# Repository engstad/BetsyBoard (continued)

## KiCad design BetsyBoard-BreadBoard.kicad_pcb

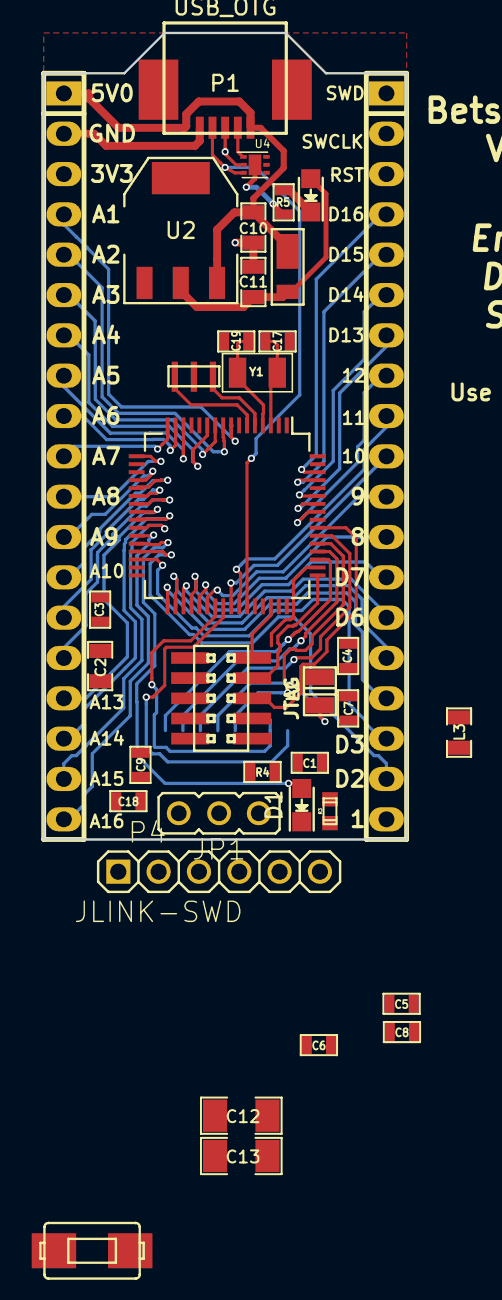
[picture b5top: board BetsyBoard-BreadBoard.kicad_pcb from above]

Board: 2 copper layers, 22.9 x 50.8 mm, 37 parts (1 on the bottom side), 60 nets.

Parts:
C1, C5, C6, C7, C8, C9, C18: 0.1uF; SM0603
C2: 4.7uF; SM0805
C3, C4: 1.0uF; SM0603
C10, C11: 10uF; SM0805
C12, C13: 22uF; SM1206
C17, C19: 10pF; SM0603
CON1: SDMMC_Card; SCHD3A0100
D1: RED; LED-0805
D2: DFLS240L; diode-smd-powerdi-123
D3: GREEN; LED-0805
JP1: JUMPER3; xess-JP2
L2: 470nF; inductor_smd_0805
L3: Bead; SM0805
P1: USB_OTG; usb-otg-short
P2, P3: CONN_01X19; pin_strip_19
P4: JLINK-SWD; HDR_1x6
P6: JTAG; conn-jtag-0.05
R3: 470; r_0603
R4: 10k; SM0603
R5: 470; SM0603
SW1: SW_PUSH; tactile-switch-te-147873-2
U1: STM32L486Rx-LQFP64; LQFP-64_10x10mm_Pitch0.5mm
U2: NCP1117ST33T3G; SOT-223
U4: PUSBM5V5X4; dfn1616-6
X1: XTAL; cstce-v-c
Y1: Crystal; CRYSTAL-32k-B

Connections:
+3.3VADC: C4.1, C9.1, L3.2, U1.13
/A1: P3.4, U1.8
/A2: P3.5, U1.9
/A3: P3.6, U1.10
/A4: P3.7, U1.11
/A5: P3.8, U1.14
/A6: P3.9, U1.15
/A7: P3.10, U1.16
/A8: P3.11, U1.17
/A9: P3.12, U1.20
/A10: P3.13, U1.21
/A11: P3.14, U1.22
/A12: P3.15, U1.23
/A13: P3.16, U1.24
/A14: P3.17, U1.25
/A15: P3.18, U1.26
/A16: P3.19, U1.27
/BOOT0: JP1.2, U1.60
/D1: D1.2, P2.19, U1.28
/D2: P2.18, U1.29
/D3: P2.17, U1.30
/D4: P2.16, U1.33
/D5: P2.15, U1.34
/D6: P2.14, U1.35
/D7: P2.13, U1.36
/D8: P2.12, U1.37
/D9: P2.11, U1.38
/D10: P2.10, U1.41
/D11: P2.9, U1.42
/D12: P2.8, U1.57
/D13: P2.7, U1.58
/D14: P2.6, U1.59
/D15: P2.5, U1.61
/D16: P2.4, U1.62
/JTCK/SWCLK: P2.2, P4.2, P6.4, U1.49
/JTDI: P6.8, U1.50
/JTDO: P6.6, U1.55
/JTMS/SWDIO: P2.1, P4.4, P6.2, U1.46
/OTG_5V: C10.1, D2.1, P1.1, P3.1, U2.3, U4.6
/OTG_FS_D+: P1.3, U1.45, U4.2
/OTG_FS_D-: P1.2, U1.44, U4.1
/OTG_FS_ID: P1.4, U1.43, U4.3
/RTC_OSC_IN: C17.1, U1.3, Y1.1
/RTC_OSC_OUT: C19.1, U1.4, Y1.2
/SDMMC_CK: CON1.5, U1.53
/SDMMC_CMD: CON1.3, U1.54
/SDMMC_D0: CON1.7, U1.39
/SDMMC_D1: CON1.8, U1.40
/SDMMC_D2: CON1.1, U1.51
/SDMMC_D3: CON1.2, U1.52
/~JTRST: C1.1, P2.3, P4.5, P6.10, SW1.2, U1.7, U1.56
GND: C1.2, C2.2, C3.2, C4.2, C5.2, C6.2, C7.2, C8.2, C9.2, C10.2, C11.2, C12.2, C13.2, C17.2, C18.2, C19.2, CON1.6, CON1.G1, CON1.G2, P1.5, P1.6, P3.2, P4.3, P6.3, P6.5, P6.9, R3.2, R4.2, R5.2, SW1.1, U1.12, U1.18, U1.31, U1.47, U1.63, U2.1, U4.7, X1.2
unnamed: C12.1, C13.1, CON1.4, L2.1
unnamed: D1.1, R3.1
unnamed: D3.1, R5.1
unnamed: JP1.1, R4.1
unnamed: U1.5, X1.1
unnamed: U1.6, X1.3
unnamed: U4.4, U4.5
VDD: C2.1, C3.1, C5.1, C6.1, C7.1, C8.1, C11.1, C18.1, D2.2, D3.2, JP1.3, L2.2, L3.1, P3.3, P4.1, P6.1, U1.1, U1.19, U1.32, U1.48, U1.64, U2.2

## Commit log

2015-09-28 Added .gitignore
2015-09-28 Last changes
2015-10-09 Changes of power source
2015-10-09 push everything to repo
2015-10-19 latest - including v0.1
2015-11-03 v0.2
2015-11-03 v0.2 gerbers
2015-11-04 More work
2015-11-04 Add bak files to be sure
2015-11-04 renaming Dipsy to Betsy
2015-11-05 This too
2015-12-09 Add BSDL files
2015-12-09 Latest
2015-12-10 Cleanup
2015-12-10 VBAT stuff
2015-12-16 Newest component
2015-12-21 Work towards v0.5
2015-12-22 Trying to fit DIP switch
2015-12-22 use git submodule for lib
2015-12-28 A little more work
2016-03-13 Move connection from NRST to /MR.
2016-08-25 Adding more pin numbers on silkscreen.
2017-04-24 v0.7
2017-04-24 More
2017-05-08 update lib
2017-05-08 small dabbles
2017-05-08 apx comments
2020-09-21 Working towards 0.9.
    - Remove NJTRST and NRST confusion
    - Remove VBUS, not needed for upstream facing port.
    - Remove shielding, don't mess with the upstream ground.
    - Put back SDMMC, it's not the same as QSPI.
    - Add README.md.
2020-09-27 More changes
2020-09-27 Fix rescued symbols
2020-09-28 Big version
2020-09-30 Changes to the BBB.
    - Fixing the QSPI_SCK problem.
    - Cleaning up.
2020-09-30 Add the first gerbers for BBB as it went to JLCPCB for order.
2020-10-09 Major changes due to mistakes
2020-10-18 More changes.
2020-10-20 Adding +5V support for I2C port, and fixing courtyard layer.
2020-10-20 sync submodule
2020-10-20 Use a battery header I can actually procure.
2020-10-23 Simplify a bit.
2020-11-02 Making more space.
2020-11-03 Fitting in bigger buttons and adding reset/boot circuit.
2020-11-04 Be relative.
2020-11-04 Don't use submodule.
2021-04-19 Additions due to single-button boot logic.
2021-04-23 Prepare for second run.
2021-05-24 Add support files for v0.2
2021-05-24 Use 4-pin QSPI NOR Flash card
2021-05-30 Version 0.9c of BetsyBoard
2021-05-30 Latest work on big version
2021-06-04 Getting ready for "final" big version.
2021-06-04 Thsi too.
2023-01-19 Save from old computer.
2024-01-05 More work on battery charging.
2024-01-12 v0.98 for production
2024-01-12 Reworking reset pin on JTAG/SWD header and adding AND-gate.
